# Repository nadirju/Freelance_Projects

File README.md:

# Freelance_Projects
This repo contains various freelance projects which I have done.

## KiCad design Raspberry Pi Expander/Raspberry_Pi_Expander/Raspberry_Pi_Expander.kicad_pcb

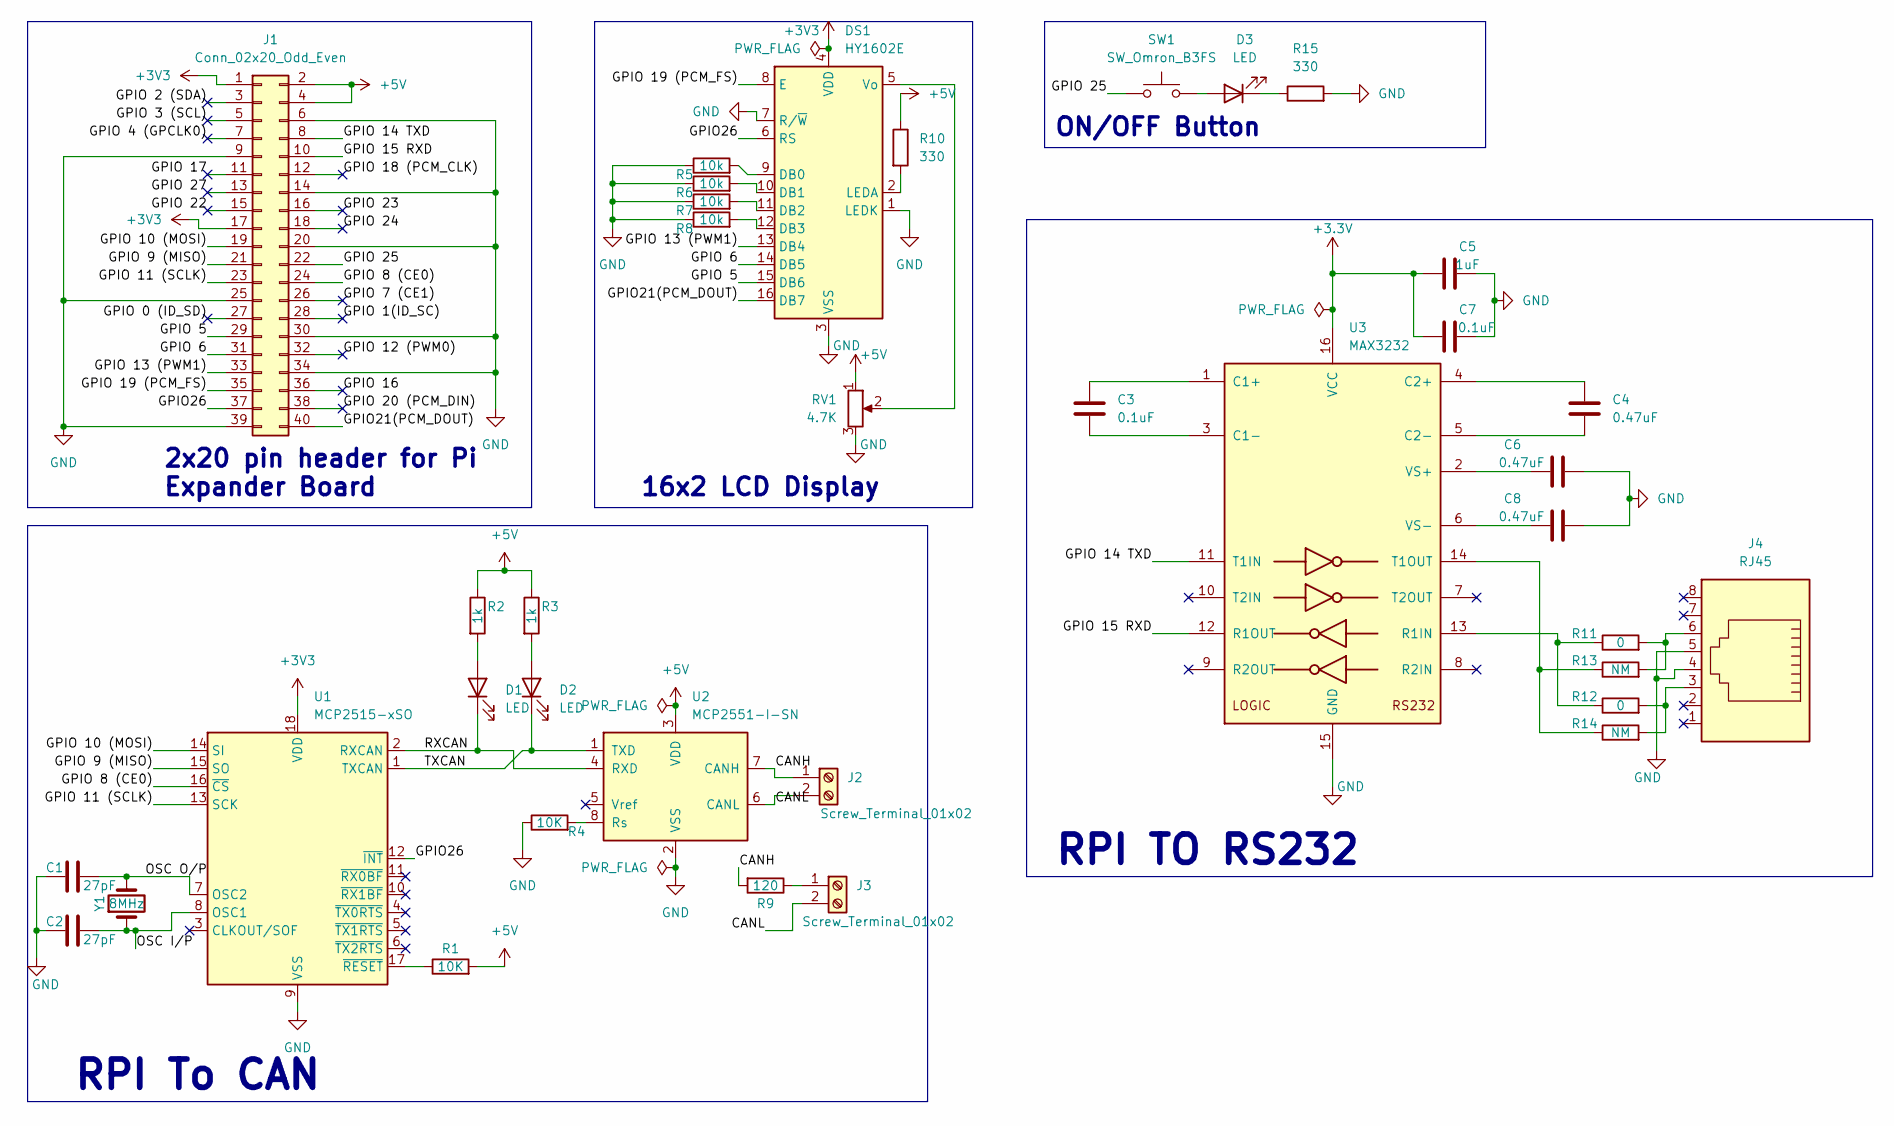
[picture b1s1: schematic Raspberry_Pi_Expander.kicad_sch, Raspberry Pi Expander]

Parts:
C1, C2: 27pF; C_0805_2012Metric
C3, C7: 0.1uF; C_0805_2012Metric
C4, C6, C8: 0.47uF; C_0805_2012Metric
C5: 1uF; C_0805_2012Metric
D1, D2, D3: LED; LED_0805_2012Metric
DS1: HY1602E
J1: Conn_02x20_Odd_Even; PinSocket_2x20_P2.54mm_Vertical
J2, J3: Screw_Terminal_01x02; TerminalBlock_bornier-2_P5.08mm
J4: RJ45; TE_RJ45-8N-B
R1, R4: 10K; R_0805_2012Metric
R2, R3: 1k; R_0805_2012Metric
R5, R6, R7, R8: 10k; R_0805_2012Metric
R9: 120; R_0805_2012Metric
R10, R15: 330; R_0805_2012Metric
R11, R12: 0; R_0805_2012Metric
R13, R14: NM; R_0805_2012Metric
RV1: 4.7K; Potentiometer_Bourns_3266Y_Vertical
SW1: SW_Omron_B3FS; SW_SPST_Omron_B3FS-100xP
U1: MCP2515-xSO; SOIC-18W_7.5x11.6mm_P1.27mm
U2: MCP2551-I-SN; SOIC-8_3.9x4.9mm_P1.27mm
U3: MAX3232; TSSOP-16_4.4x5mm_P0.65mm
Y1: 8MHz; Crystal_HC49-4H_Vertical

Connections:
+3.3V: C5.1, C7.1, U3.16 (VCC)
+3V3: DS1.4 (VDD), J1.1, J1.17, U1.18 (VDD)
+5V: J1.2, J1.4, R1.2, R2.1, R3.1, R10.1, RV1.1, U2.3 (VDD)
/CANH: J2.1, R9.2, U2.7 (CANH)
/CANL: J2.2, J3.2, U2.6 (CANL)
/GPIO21(PCM_DOUT): DS1.16 (DB7), J1.40
/GPIO26: DS1.6 (RS), J1.37, U1.12 (~INT)
/GPIO 0 (ID_SD): J1.27
/GPIO 1(ID_SC): J1.28
/GPIO 2 (SDA): J1.3
/GPIO 3 (SCL): J1.5
/GPIO 4 (GPCLK0): J1.7
/GPIO 5: DS1.15 (DB6), J1.29
/GPIO 6: DS1.14 (DB5), J1.31
/GPIO 7 (CE1): J1.26
/GPIO 8 (CE0): J1.24, U1.16 (~CS)
/GPIO 9 (MISO): J1.21, U1.15 (SO)
/GPIO 10 (MOSI): J1.19, U1.14 (SI)
/GPIO 11 (SCLK): J1.23, U1.13 (SCK)
/GPIO 12 (PWM0): J1.32
/GPIO 13 (PWM1): DS1.13 (DB4), J1.33
/GPIO 14 (TXD): J1.8, U3.11 (T1IN)
/GPIO 15 (RXD): J1.10, U3.12 (R1OUT)
/GPIO 16: J1.36
/GPIO 17: J1.11
/GPIO 18 (PCM_CLK): J1.12
/GPIO 19 (PCM_FS): DS1.8 (E), J1.35
/GPIO 20 (PCM_DIN): J1.38
/GPIO 22: J1.15
/GPIO 23: J1.16
/GPIO 24: J1.18
/GPIO 25: J1.22, SW1.1
/GPIO 27: J1.13
/OSC I/P: C2.2, U1.8 (OSC1), Y1.1
/OSC O/P: C1.2, U1.7 (OSC2), Y1.2
/RXCAN: D1.1 (K), U1.2 (RXCAN), U2.4 (RXD)
/TXCAN: D2.1 (K), U1.1 (TXCAN), U2.1 (TXD)
GND: C1.1, C2.1, C5.2, C6.2, C7.2, C8.2, DS1.1 (LEDK), DS1.3 (VSS), DS1.7 (R/~W), J1.6, J1.9, J1.14, J1.20, J1.25, J1.30, J1.34, J1.39, J4.4, J4.5, R4.1, R5.1, R6.1, R7.1, R8.1, R15.2, RV1.3, U1.9 (VSS), U2.2 (VSS), U3.15 (GND)
unnamed: D1.2 (A), R2.2
unnamed: D2.2 (A), R3.2
unnamed: D3.2 (A), SW1.2
unnamed: D3.1 (K), R15.1
unnamed: DS1.9 (DB0), R5.2
unnamed: DS1.10 (DB1), R6.2
unnamed: DS1.11 (DB2), R7.2
unnamed: DS1.12 (DB3), R8.2
unnamed: DS1.2 (LEDA), R10.2
unnamed: DS1.5 (Vo), RV1.2
unnamed: J3.1, R9.1
unnamed: J4.3, R12.2, R14.2
unnamed: J4.6, R11.2, R13.2
unnamed: R1.1, U1.17 (~RESET)
unnamed: R4.2, U2.8 (Rs)
unnamed: C3.1, U3.1 (C1+)
unnamed: C3.2, U3.3 (C1-)
unnamed: C4.1, U3.4 (C2+)
unnamed: C4.2, U3.5 (C2-)
unnamed: R11.1, R12.1, U3.13 (R1IN)
unnamed: R13.1, R14.1, U3.14 (T1OUT)
unnamed: C6.1, U3.2 (VS+)
unnamed: C8.1, U3.6 (VS-)

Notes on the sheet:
RPI To CAN
16x2 LCD Display
2x20 pin header for Pi Expander Board
ON/OFF Button
RPI TO RS232

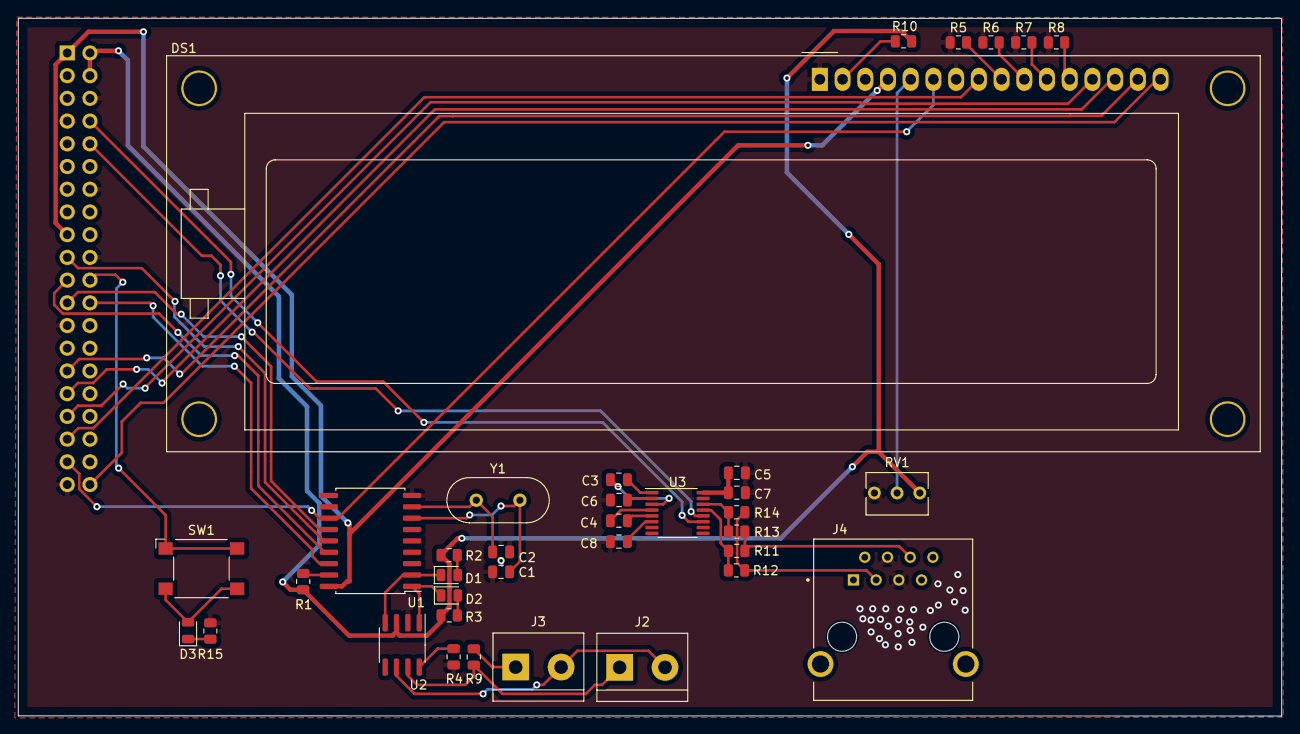
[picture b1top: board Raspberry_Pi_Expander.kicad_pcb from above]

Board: 2 copper layers, 141.3 x 78.0 mm, 37 parts (1 on the bottom side), 46 nets.
